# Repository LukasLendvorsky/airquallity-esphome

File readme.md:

# AirquaLLity-esphome

Air-quality sensor (CO2, particulate matter, ...) in a nice 3D printed package with LED bar visualization. Using ESPHome, compatible with HomeAssitant.

## Images

## Features
- Wi-Fi
- RGB LED bar for quick visual air-quality indication
- HomeAssistant compatible

### Sensors:
 - Accurate CO2 using dual NDIR sensor (SCD30) 
 - Particulate matter (<10µm, <2.5µm, <1µm)
 - Temperature
 - Humidity
 - Illumination (amount of light)
 - VOC (Volatile organic compound) sensor
 - NOx sensor

## How to build

Manufactury files available, see schematic/jlcpcb. They can assemble most of the bord, however you'll need to solder at least CO2 sensor & particulate matter sensor yourself.

## Firmware 
 See https://esphome.io/guides/getting_started_command_line.html

- set your Wi-Fi credentials in firmware\secrets.yaml
- go to firmware directory
- Run: ```esphome run llairquality.yaml```

## License

See [LICENSE](LICENSE)

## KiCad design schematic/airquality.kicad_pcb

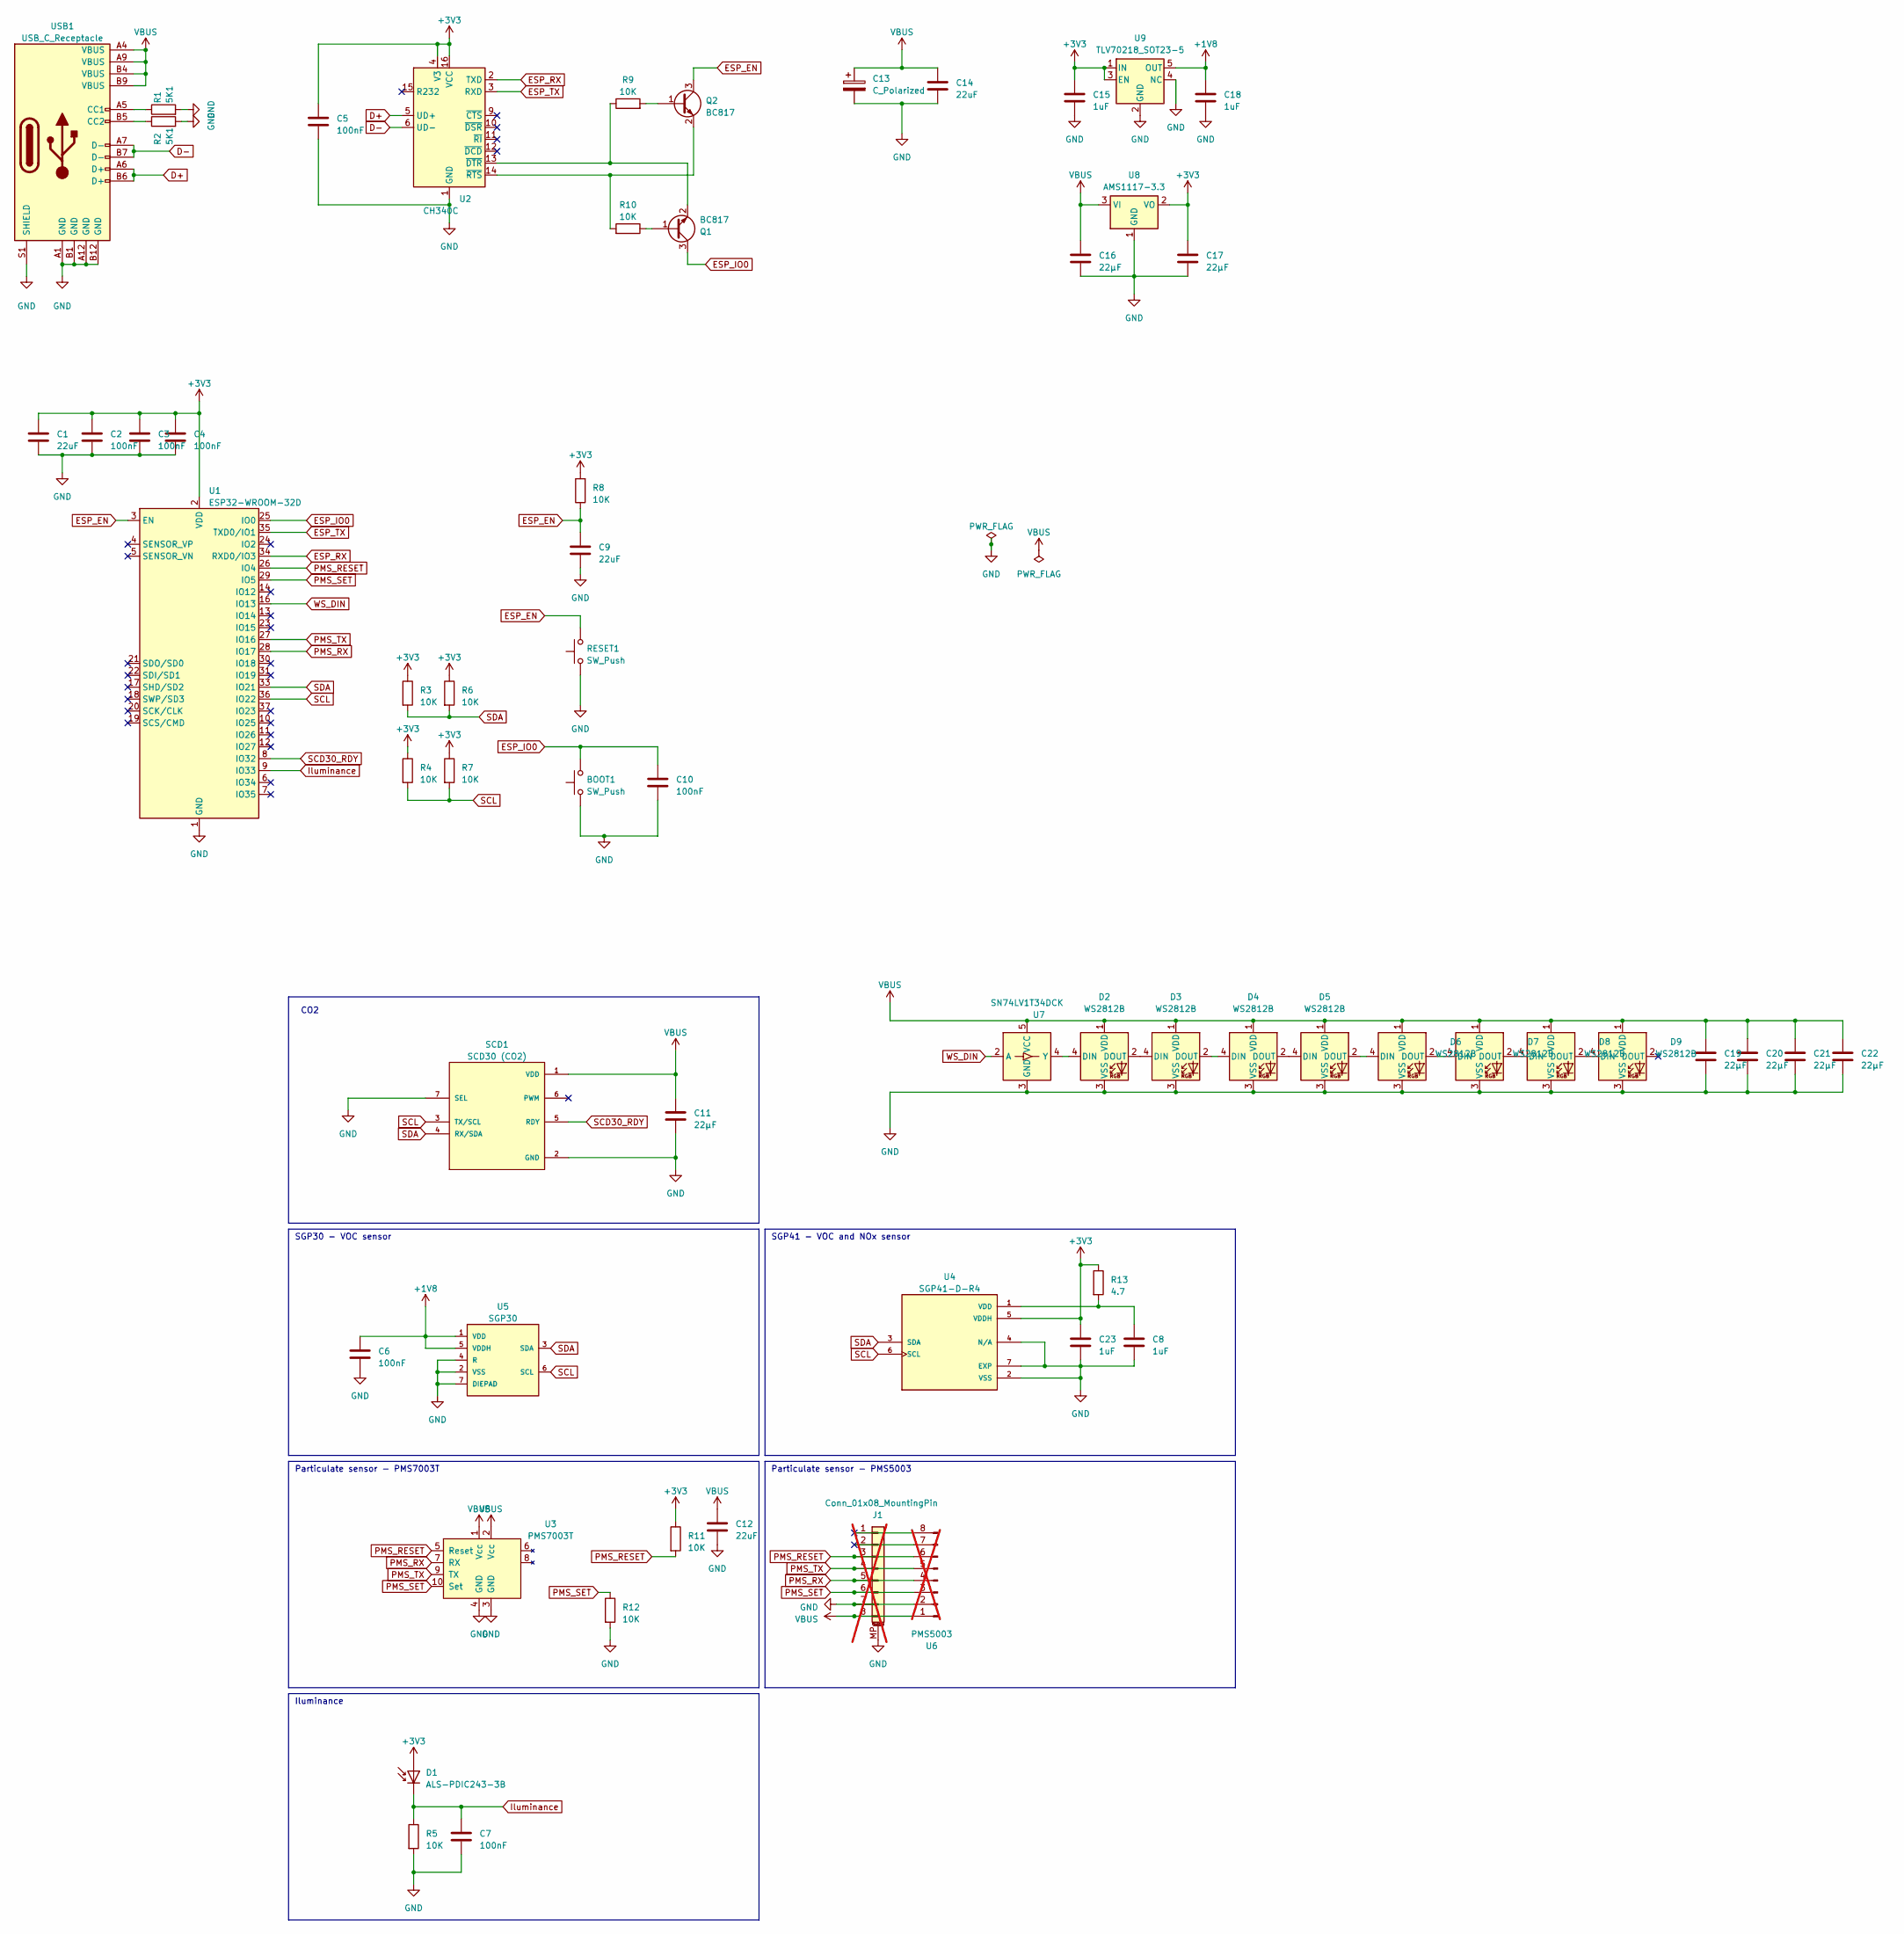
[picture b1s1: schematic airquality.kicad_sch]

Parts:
BOOT1: SW_Push; GT-TC029B-H025-L1N
C1, C9, C12, C14: 22uF; C_0603_1608Metric
C2, C3, C4, C5, C6, C7, C10: 100nF; C_0603_1608Metric
C8, C15, C18, C23: 1uF; C_0603_1608Metric
C11, C16, C17, C19, C20, C21, C22: 22µF; C_0603_1608Metric
C13: C_Polarized; CP_Elec_6.3x5.4
D1: ALS-PDIC243-3B
D2, D3, D4, D5, D6, D7, D8, D9: WS2812B; LED_WS2812B_PLCC4_5.0x5.0mm_P3.2mm
J1: Conn_01x08_MountingPin; Molex_PicoBlade_53261-0871_1x08-1MP_P1.25mm_Horizontal; not fitted
Q1, Q2: BC817; SOT-23
R1, R2: 5K1; R_0603_1608Metric
R3, R4, R5, R6, R7, R8, R9, R10, R11, R12: 10K; R_0603_1608Metric
R13: 4.7; R_0603_1608Metric
RESET1: SW_Push; GT-TC029B-H025-L1N
SCD1: SCD30 (CO2); MODULE_SCD30; PARTREV D1
U1: ESP32-WROOM-32D
U2: CH340C; SOIC-16_3.9x9.9mm_P1.27mm
U3: PMS7003T; PMS7003
U4: SGP41-D-R4; XDCR_SGP41-D-R4; PARTREV 1.0
U5: SGP30
U6: PMS5003; not fitted
U7: SN74LV1T34DCK; SOT-353_SC-70-5
U8: AMS1117-3.3; SOT-223-3_TabPin2
U9: TLV70218_SOT23-5; SOT-23-5
USB1: USB_C_Receptacle; Hanbo Electronic MC-802YC-H100

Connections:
+1V8: C6.1, C18.1, U5.1 (VDD), U5.5 (VDDH), U9.5 (OUT)
+3V3: C1.1, C2.1, C3.1, C4.1, C5.1, C15.1, C17.1, C23.1, D1.2 (A), R3.1, R4.1, R6.1, R7.1, R8.2, R11.1, R13.1, U1.2 (VDD), U2.4 (V3), U2.16 (VCC), U4.5 (VDDH), U8.2 (VO), U9.1 (IN), U9.3 (EN)
D+: U2.5 (UD+), USB1.A6 (D+), USB1.B6 (D+)
D-: U2.6 (UD-), USB1.A7 (D-), USB1.B7 (D-)
ESP_EN: C9.1, Q2.3 (C), R8.1, RESET1.2, U1.3 (EN)
ESP_IO0: BOOT1.2, C10.1, Q1.3 (C), U1.25 (IO0)
ESP_RX: U1.34 (RXD0/IO3), U2.2 (TXD)
ESP_TX: U1.35 (TXD0/IO1), U2.3 (RXD)
GND: BOOT1.1, C1.2, C2.2, C3.2, C4.2, C5.2, C6.2, C7.2, C8.2, C9.2, C10.2, C11.2, C12.2, C13.2, C14.2, C15.2, C16.2, C17.2, C18.2, C19.2, C20.2, C21.2, C22.2, C23.2, D2.3 (VSS), D3.3 (VSS), D4.3 (VSS), D5.3 (VSS), D6.3 (VSS), D7.3 (VSS), D8.3 (VSS), D9.3 (VSS), J1.7, J1.MP (MountPin), R1.2, R2.2, R5.2, R12.2, RESET1.1, SCD1.2 (GND), SCD1.7 (SEL), U1.1 (GND), U1.15 (GND), U1.38 (GND), U1.39 (GND), U2.1 (GND), U3.3 (GND), U3.4 (GND), U4.2 (VSS), U4.4 (N/A), U4.7 (EXP), U5.2 (VSS), U5.4 (R), U5.7 (DIEPAD), U6.2, U7.3 (GND), U8.1 (GND), U9.2 (GND), U9.4 (NC), USB1.A1 (GND), USB1.A12 (GND), USB1.B1 (GND), USB1.B12 (GND), USB1.S1 (SHIELD)
Iluminance: C7.1, D1.1 (K), R5.1, U1.9 (IO33)
unnamed: D2.4 (DIN), U7.4 (Y)
unnamed: D2.2 (DOUT), D3.4 (DIN)
unnamed: D3.2 (DOUT), D4.4 (DIN)
unnamed: D4.2 (DOUT), D5.4 (DIN)
unnamed: D5.2 (DOUT), D6.4 (DIN)
unnamed: D6.2 (DOUT), D7.4 (DIN)
unnamed: D7.2 (DOUT), D8.4 (DIN)
unnamed: D8.2 (DOUT), D9.4 (DIN)
unnamed: J1.1, U6.8
unnamed: J1.2, U6.7
unnamed: Q1.1 (B), R10.1
unnamed: Q1.2 (E), R9.1, U2.13 (~DTR)
unnamed: Q2.1 (B), R9.2
unnamed: Q2.2 (E), R10.2, U2.14 (~RTS)
unnamed: C8.1, R13.2, U4.1 (VDD)
unnamed: R1.1, USB1.A5 (CC1)
unnamed: R2.1, USB1.B5 (CC2)
PMS_RESET: J1.3, R11.2, U1.26 (IO4), U3.5 (Reset), U6.6
PMS_RX: J1.5, U1.28 (IO17), U3.7 (RX), U6.4
PMS_SET: J1.6, R12.1, U1.29 (IO5), U3.10 (Set), U6.3
PMS_TX: J1.4, U1.27 (IO16), U3.9 (TX), U6.5
SCD30_RDY: SCD1.5 (RDY), U1.8 (IO32)
SCL: R4.2, R7.2, SCD1.3 (TX/SCL), U1.36 (IO22), U4.6 (SCL), U5.6 (SCL)
SDA: R3.2, R6.2, SCD1.4 (RX/SDA), U1.33 (IO21), U4.3 (SDA), U5.3 (SDA)
VBUS: C11.1, C12.1, C13.1, C14.1, C16.1, C19.1, C20.1, C21.1, C22.1, D2.1 (VDD), D3.1 (VDD), D4.1 (VDD), D5.1 (VDD), D6.1 (VDD), D7.1 (VDD), D8.1 (VDD), D9.1 (VDD), J1.8, SCD1.1 (VDD), U3.1 (Vcc), U3.2 (Vcc), U6.1, U7.5 (VCC), U8.3 (VI), USB1.A4 (VBUS), USB1.A9 (VBUS), USB1.B4 (VBUS), USB1.B9 (VBUS)
WS_DIN: U1.16 (IO13), U7.2 (A)

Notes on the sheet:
Iluminance
Particulate sensor - PMS5003
CO2
SGP30 - VOC sensor
SGP41 - VOC and NOx sensor
Particulate sensor - PMS7003T

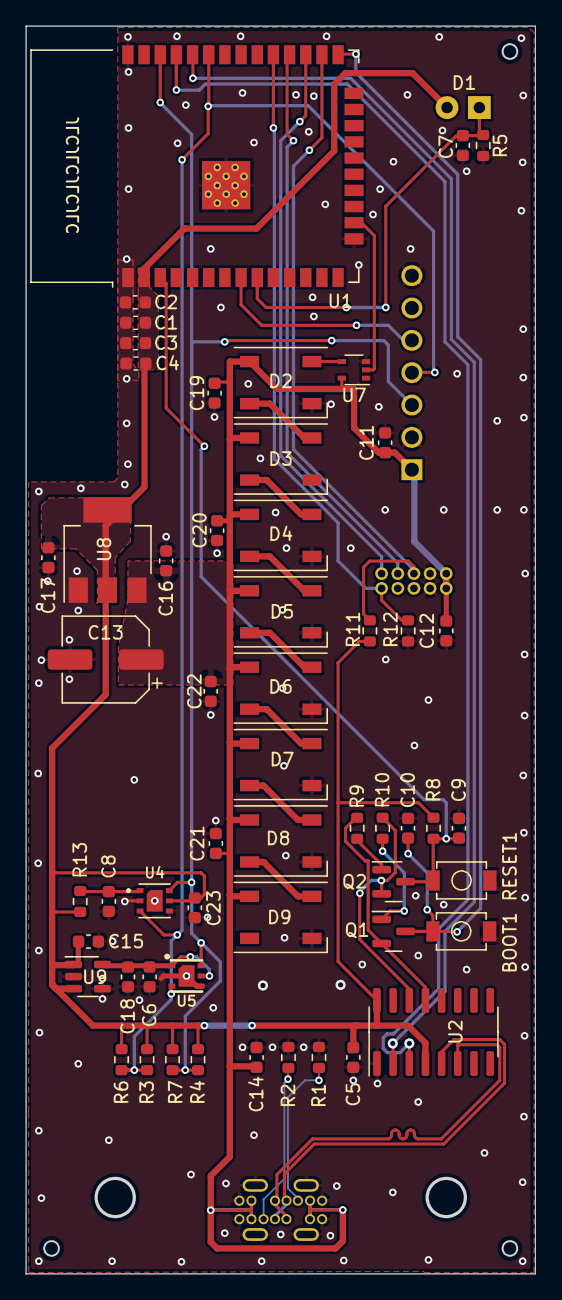
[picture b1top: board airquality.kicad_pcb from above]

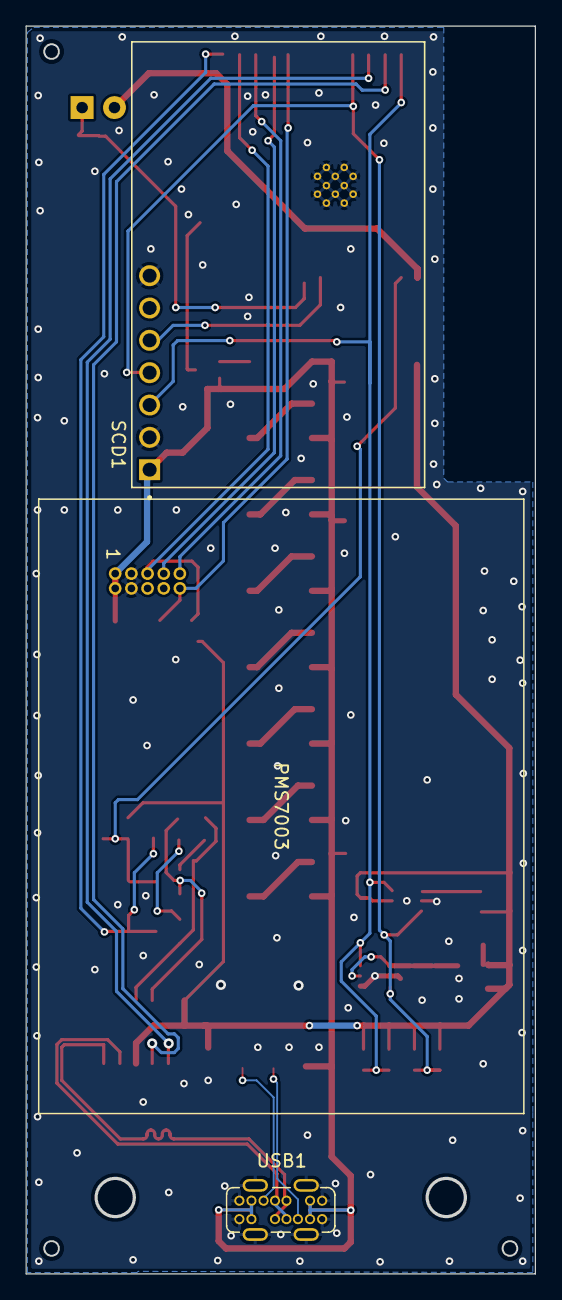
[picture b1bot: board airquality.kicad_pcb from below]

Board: 2 copper layers, 39.8 x 97.8 mm, 59 parts (3 on the bottom side), 34 nets.

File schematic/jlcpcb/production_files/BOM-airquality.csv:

Comment,Designator,Footprint,LCSC
ALS-PDIC243-3B,D1,ALS-PDIC243-3B,C141718
100nF,"C10,C2,C3,C4,C5,C6,C7",C_0603_1608Metric,C14663
5K1,"R1,R2",R_0603_1608Metric,C14677
SCD30 (CO2),SCD1,MODULE_SCD30,C1519271
1uF,"C15,C18,C23,C8",C_0603_1608Metric,C15849
BC817,"Q1,Q2",SOT-23,C2137
4.7,R13,R_0603_1608Metric,C23164
10K,"R10,R11,R12,R3,R4,R5,R6,R7,R8,R9",R_0603_1608Metric,C25804
WS2812B,"D2,D3,D4,D5,D6,D7,D8,D9",LED_WS2812B_PLCC4_5.0x5.0mm_P3.2mm,C2761795
USB_C_Receptacle,USB1,Hanbo Electronic MC-802YC-H100,C3039300
SGP41-D-R4,U4,XDCR_SGP41-D-R4,C3659325
TLV70218_SOT23-5,U9,SOT-23-5,C44435
SGP30,U5,SGP30,C514454
ESP32-WROOM-32D,U1,ESP32-WROOM-32D,C529577
22uF,"C1,C11,C12,C14,C16,C17,C19,C20,C21,C22,C9",C_0603_1608Metric,C59461
AMS1117-3.3,U8,SOT-223-3_TabPin2,C6186
C_Polarized,C13,CP_Elec_6.3x5.4,C72494
SN74LV1T34DCK,U7,SOT-353_SC-70-5,C78541
SW_Push,"BOOT1,RESET1",GT-TC029B-H025-L1N,C843669
CH340C,U2,SOIC-16_3.9x9.9mm_P1.27mm,C84681
PMS7003T,U3,PMS7003,

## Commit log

2023-04-09 Initial version
2023-04-09 Fix orientation of particulate sensor
2023-04-09 JLCPCB parts assignment
2023-04-09 cleanup
2023-04-09 Fix ESP32 model
2023-04-09 PMS700 silk screen on correct side
2023-04-09 MInor silkscreen fixes
2023-04-09 jlcpcb component assignment
2023-04-11 Fix iluminance pin, add caps, add optional double pullups for I2C, cleaup
2023-04-18 Lots of fixes
2023-04-22 swap PMS7003 with PMS5003
2023-04-22 jlc assignment fixed
2023-04-22 Mounting holes
2023-04-22 jlcpcb export
2023-05-14 Add firmware
2023-05-14 Somewhat working fw
2023-07-28 fw updated for next revision
2023-07-28 New board revision
2023-07-30 Case
2023-12-03 Create LICENSE
2023-12-03 Updated FW
2023-12-03 Add readme
2023-12-03 Add commented SGP30 sensor
2023-12-03 Secrets example
2023-12-03 Add board images
